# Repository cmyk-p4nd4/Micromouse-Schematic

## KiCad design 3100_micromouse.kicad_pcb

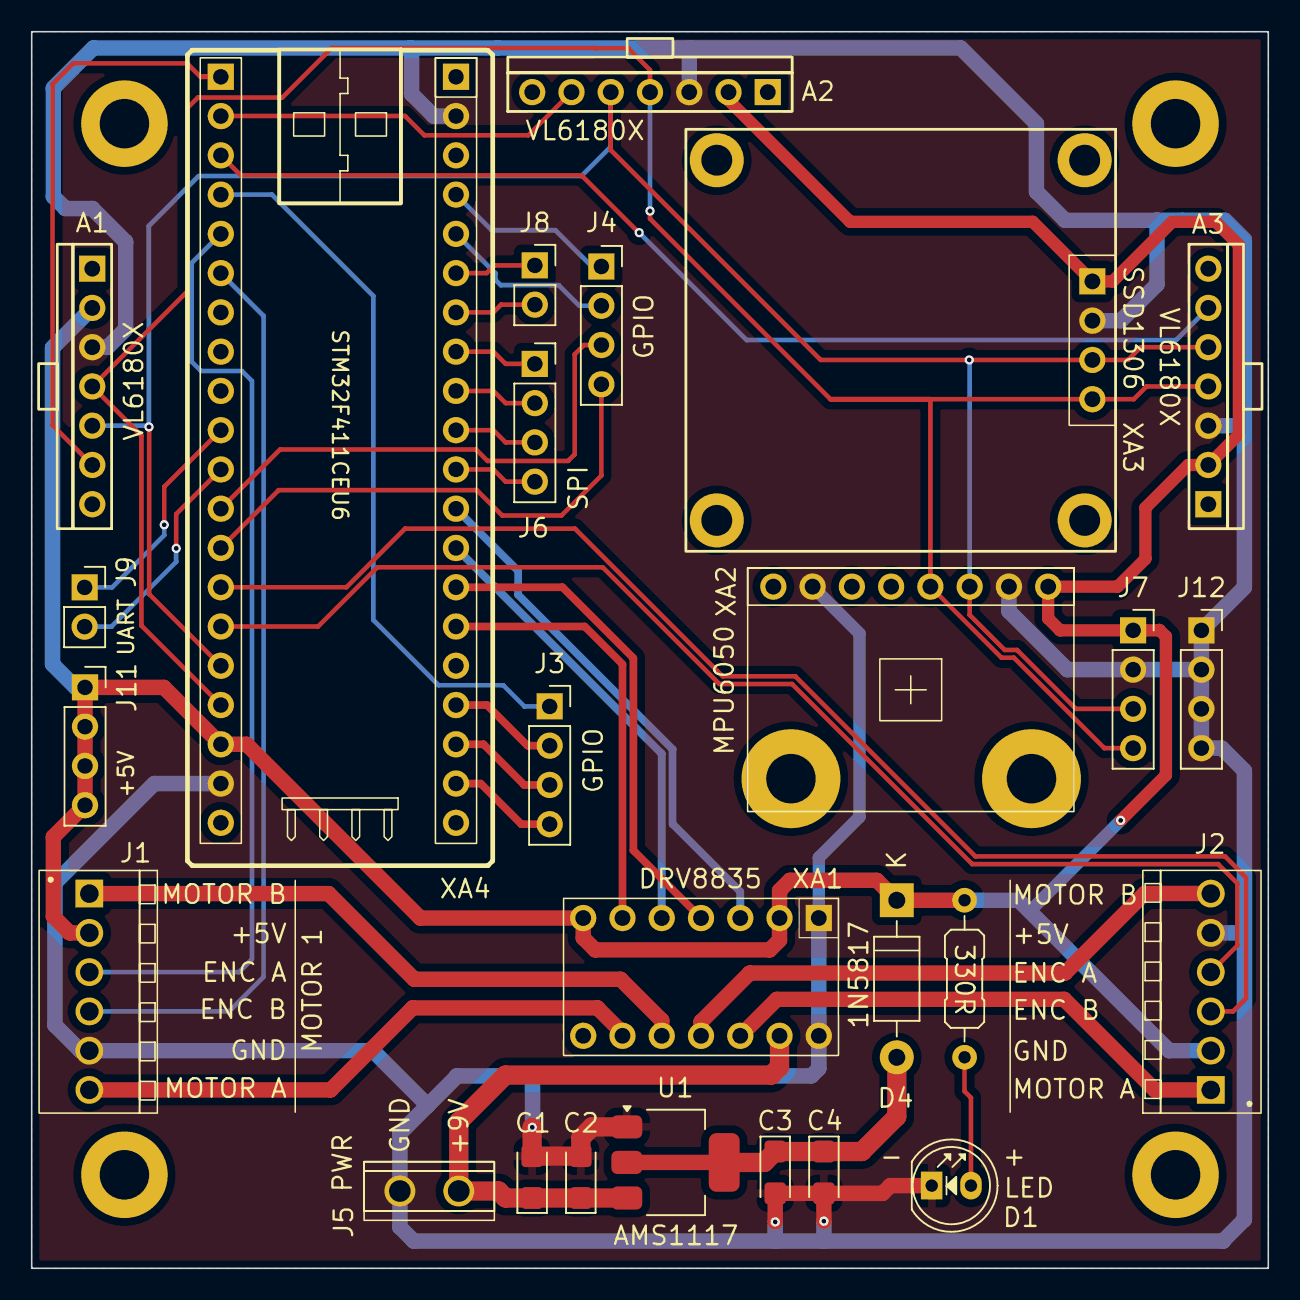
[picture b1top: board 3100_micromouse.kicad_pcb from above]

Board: 2 copper layers, 80.0 x 80.0 mm, 30 parts (0 on the bottom side), 38 nets.

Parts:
A1, A2, A3: VL6180X; VL6180X_Module_Vertical
C1, C2: 10uF; CP_EIA-3216-18_Kemet-A
C3, C4: 22uF; CP_EIA-3216-18_Kemet-A
D1: Green LED; LED_D5.0mm
D4: 1N5817; D_DO-41_SOD81_P10.16mm_Horizontal
H1, H2, H3, H4: MountingHole; MountingHole_3.2mm_M3_DIN965_Pad
J1: MOTOR1; TE_Terminal_3.81_6P
J2: MOTOR2; TE_Terminal_3.81_6P
J3: Extra GPIO A; PinSocket_1x04_P2.54mm_Vertical
J4: Extra GPIO B; PinSocket_1x04_P2.54mm_Vertical
J5: 2 Pin PWR; KEFA_KF2EDGR_3.81_2P
J6: Aux SPI Bus; PinSocket_1x04_P2.54mm_Vertical
J7: Aux I2C Bus; PinSocket_1x04_P2.54mm_Vertical
J8: Extra Analog Pins; PinSocket_1x02_P2.54mm_Vertical
J9: UART Interface; PinSocket_1x02_P2.54mm_Vertical
J11, J12: Extra +5V; PinSocket_1x04_P2.54mm_Vertical
R1: 330R; R_Axial_DIN0207_L6.3mm_D2.5mm_P10.16mm_Horizontal
U1: AMS1117-5.0; SOT-223-3_TabPin2
XA1: DRV8835; DRV8835_Module
XA2: MPU6050; MPU6050_Module
XA3: SSD1306; SSD1306_OLED_Module
XA4: STM32F411CEU6; STM32F411_BlackPill_Socket

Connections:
+5V: A1.2 (VIN), A2.2 (VIN), A3.2 (VIN), D4.1 (K), J1.2, J2.2, J7.1, J11.1, J11.2, J11.3, J11.4, R1.1, XA1.2 (VCC), XA1.7 (MODE), XA2.1 (VCC), XA3.1 (VCC), XA4.18, XA4.40
+9V: C1.1, C2.1, J5.1, U1.3 (VIN), XA1.13 (VIN)
/AIN8: J8.1, XA4.35
/AIN9: J8.2, XA4.34
/B2: J4.2, XA4.36
/B4: J4.3, XA4.12
/B5: J4.4, XA4.13
/B10: J4.1, XA4.37
/B15: J3.1, XA4.4
/C12: J3.4, XA4.22
/C13: J3.3, XA4.23
/C14: J3.2, XA4.24
/DIR1: XA1.6 (APH), XA4.26
/DIR2: XA1.4 (BPH), XA4.27
/ENC1A: J1.3, XA4.5
/ENC1B: J1.4, XA4.6
/ENC2A: J2.3, XA4.14
/ENC2B: J2.4, XA4.15
/MISO: J6.2, XA4.32
/MOSI: J6.1, XA4.33
/MOTOR1A: J1.6, XA1.9 (AOUT1)
/MOTOR1B: J1.1, XA1.10 (AOUT2)
/MOTOR2A: J2.6, XA1.11 (BOUT1)
/MOTOR2B: J2.1, XA1.12 (BOUT2)
/PWM1: XA1.5 (AEN), XA4.28
/PWM2: XA1.3 (BEN), XA4.29
/SCK: J6.3, XA4.31
/SCL: A1.5 (SCL), A2.5 (SCL), A3.5 (SCL), J7.3, XA2.3 (SCL), XA3.3 (SCL), XA4.16
/SDA: A1.4 (SDA), A2.4 (SDA), A3.4 (SDA), J7.4, XA2.4 (SDA), XA3.4 (SDA), XA4.17
/TRIG1: A1.6 (GPIO0), XA4.1
/TRIG2: A2.6 (GPIO0), XA4.2
/TRIG3: A3.6 (GPIO0), XA4.3
/UART_RX: J9.2, XA4.11
/UART_TX: J9.1, XA4.10
/~CS: J6.4, XA4.30
GNDREF: A1.3 (GND), A2.3 (GND), A3.3 (GND), C1.2, C2.2, C3.2, C4.2, D1.1 (K), J1.5, J2.5, J5.2, J7.2, J12.1, J12.2, J12.3, J12.4, U1.1 (GND), XA1.1 (GND), XA1.14 (GND), XA2.2 (GND), XA2.7 (ADO), XA3.2 (GND), XA4.19, XA4.39
unnamed: D1.2 (A), R1.2
unnamed: C3.1, C4.1, D4.2 (A), U1.2 (+5V)

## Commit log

2025-06-19 Initial Commit with Schematics completed
2025-06-19 Completed MPU6050 & DRV8835 Module Footprint - Also added step models
2025-06-22 Added Footprint model for all components except connectors
2025-06-23 Finished All footprints - PCB placement done momemtarily - plus wiring buck convertor done
2025-06-24 Changed TOF Trigger pins to B12-14 - also removed 3V3 access as board space are running out
2025-06-24 Finialized and Finished PCB routing
2025-06-24 Delete fp-info-cache
    Not intend to be added
